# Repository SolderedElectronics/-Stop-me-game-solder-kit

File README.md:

# DIY_Stop_Me_Game_Kit

# Description and details
"Stop Me" game is small and simple game running on ATtiny13 microcontroller. It consists of 7 LEDs, push button, small CR2032 battery and microcontroller. The game starts with LEDs lightning up in sequential order. LED in the middle (4th in row) is different color in comparison to the rest of the LEDs. Goal of the game is very simple, player must press the push button when the middle LED (only one in different color) is light up. If the correct LED is turned on when the push button is pressed, the player goes on next level where time delay between LED lighting up is shortened. If any other LED is turned on when the push button is pressed, the game restarts to the first level. The game is designed to have multiple levels (12 in total). 

This game is designed as a DIY soldering kit. This kit is ideal for kids and soldering beginners who can exercise their skills with this simple & easy game. While learning to solder, you will also create unique gadget which you can carry around. In addition, while playing this simple game, players can exercise their reflex skills.

# Repository content

This repo is divided into two parts: Eagle Files and Firmware. Eagle Files folder contains Cadsoft Eagle .sch and .brd files for "Stop Me" game PCB board. in addition there is schematic in .pdf created from .sch eagle file. In Firmware folder you can find C code for programming ATtiny13 microcontroller. The entire program code uses less than 1kB of Flash memory.

# Instructions on soldering

1. Insert the 8 pin IC socket into IC. Flip the board over, then solder into place.
2. Insert the switch and pushbutton into S1 and S2. Flip the board over and solder into place.
3. Insert 7 LEDs into LED1, LED2, LED2, LED3, LED4, LED5, LED6. Each LED has a short leg and a long leg. The long leg goes into the hole closest to the "+" sign on the board. NOTE: The green LED goes into LED4 place. Flip the board over, then solder into place.
4. Flip the board over. Put CR2032 battery holder into BAT place. Don't put battery in holder just yet. Flip the board over again and solder into place. The battery holder is only piece which is soldered on the back side of PCB.
5. Insert Attiny13 microcontroller into 8 pin IC socket. Make sure the dot in the corner of the chip is on bottom left corner.
6. Insert CR2032 battery into soldered battery holder.
7. Yay you're done! Flip the switch to the ON position and the game should start. Have Fun playing it. 

# Board versions
- v1.0 - initial version

# License info
This product is open-source. YAY!

e-radionica.com Team.

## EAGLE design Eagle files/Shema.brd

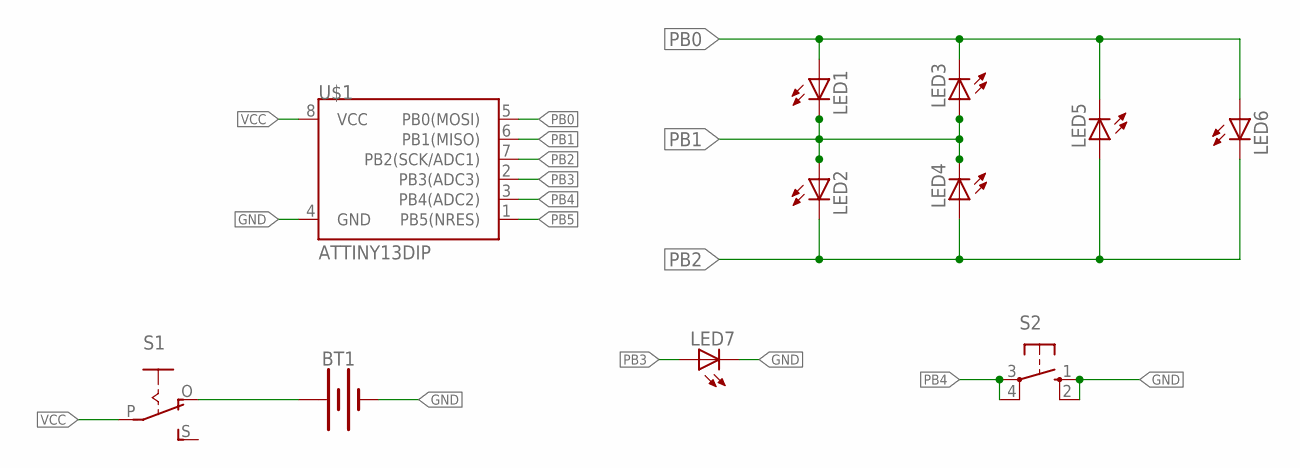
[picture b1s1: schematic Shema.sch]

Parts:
BT1: BATTERY-20MM_PTH; BATTCOM_20MM_PTH
LED1, LED2, LED3, LED4, LED5, LED6, LED7: LED5MM
S1: EG1218S; EG1218
S2: 40-XX; B3F-40XX
U$1: ATTINY13DIP; DIP08_MCU

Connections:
GND: BT1.2 (-), LED7.K (C), S2.1 (S), S2.2 (S1), U$1.4 (GND)
unnamed: BT1.1 (+), S1.O
PB0: LED1.A, LED3.K (C), LED5.K (C), LED6.A, U$1.5 (PB0(MOSI))
PB1: LED1.K (C), LED2.A, LED3.A, LED4.K (C), U$1.6 (PB1(MISO))
PB2: LED2.K (C), LED4.A, LED5.A, LED6.K (C), U$1.7 (PB2(SCK/ADC1))
PB3: LED7.A, U$1.2 (PB3(ADC3))
PB4: S2.3, S2.4 (P1), U$1.3 (PB4(ADC2))
PB5: U$1.1 (PB5(NRES))
VCC: S1.P, U$1.8 (VCC)

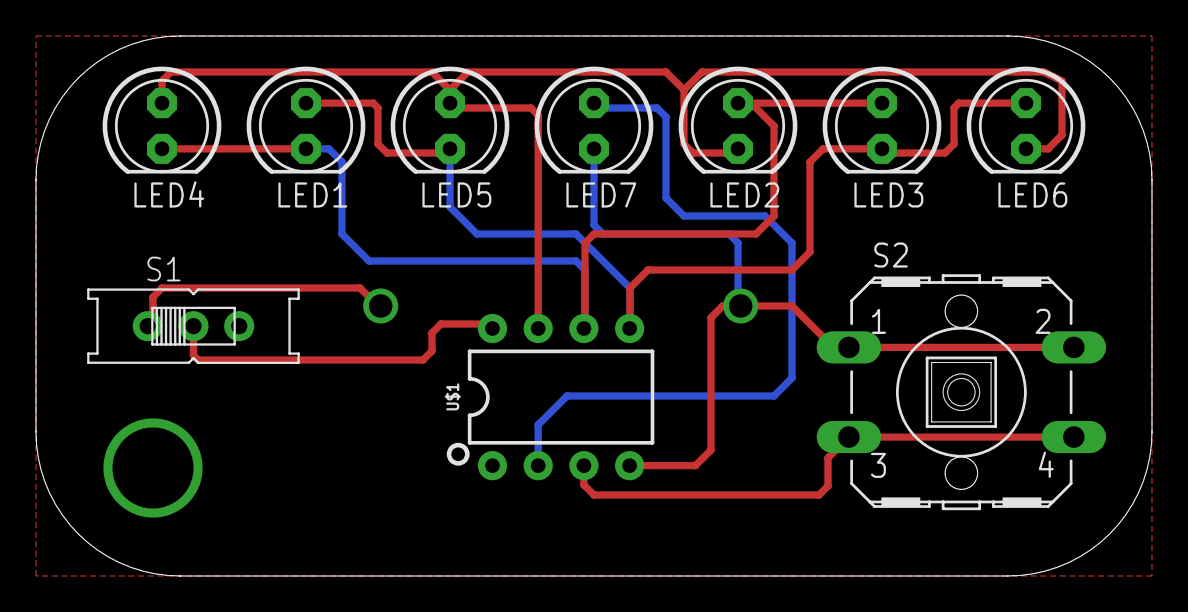
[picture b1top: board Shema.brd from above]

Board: 2 copper layers, 62.0 x 30.0 mm, 11 parts (1 on the bottom side), 8 nets.

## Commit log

2018-05-22 DIY "Stop Me" Soldering kit
    DIY "Stop Me" Soldering kit

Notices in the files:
parts and their libraries:
SparkFun-Batteries: Licensing: Creative Commons ShareAlike 4.0 International - https://creativecommons.org/licenses/by-sa/4.0
